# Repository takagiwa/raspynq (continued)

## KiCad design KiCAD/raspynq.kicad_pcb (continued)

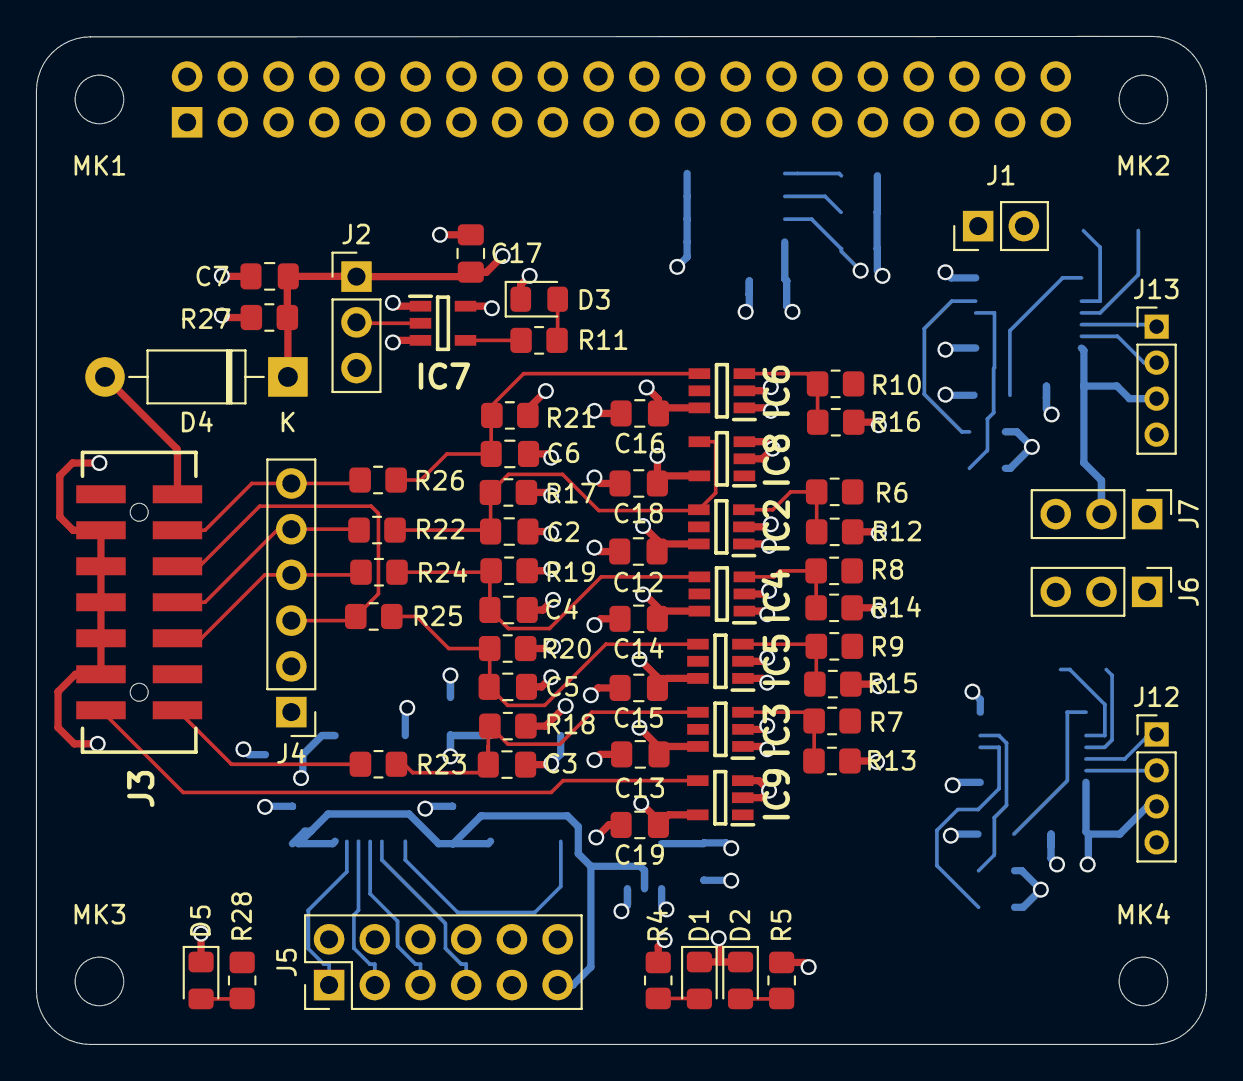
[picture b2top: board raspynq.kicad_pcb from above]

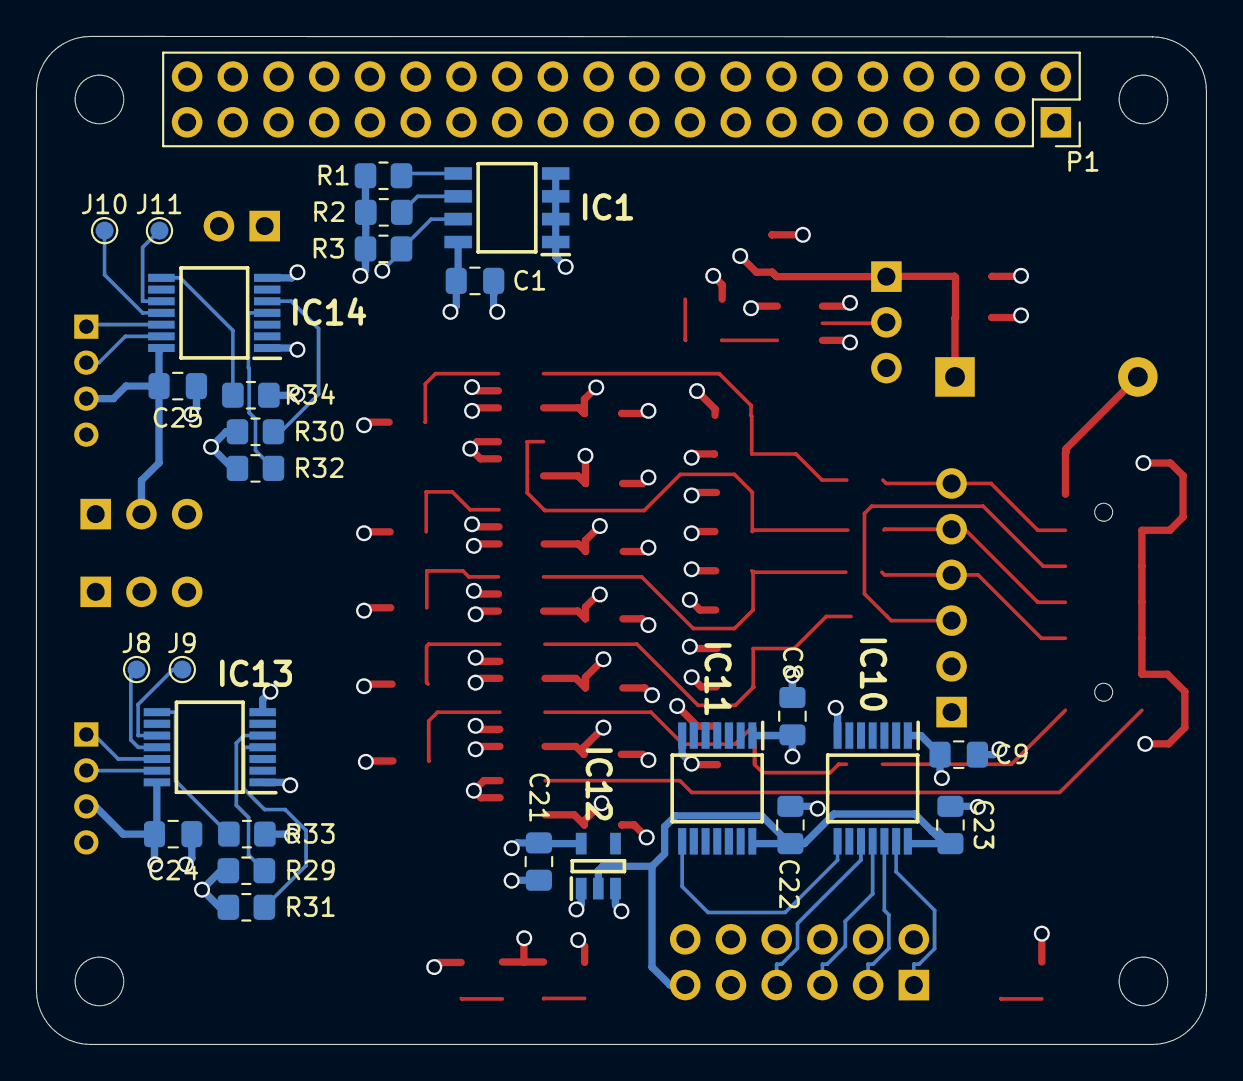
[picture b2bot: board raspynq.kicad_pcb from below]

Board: 4 copper layers, 65.0 x 56.0 mm, 93 parts (28 on the bottom side), 81 nets.

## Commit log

2022-02-13 gave up routing. decided to divide two boards (JTAG and others).
2022-02-20 first version of base JTAG interface
2023-02-27 initial version
